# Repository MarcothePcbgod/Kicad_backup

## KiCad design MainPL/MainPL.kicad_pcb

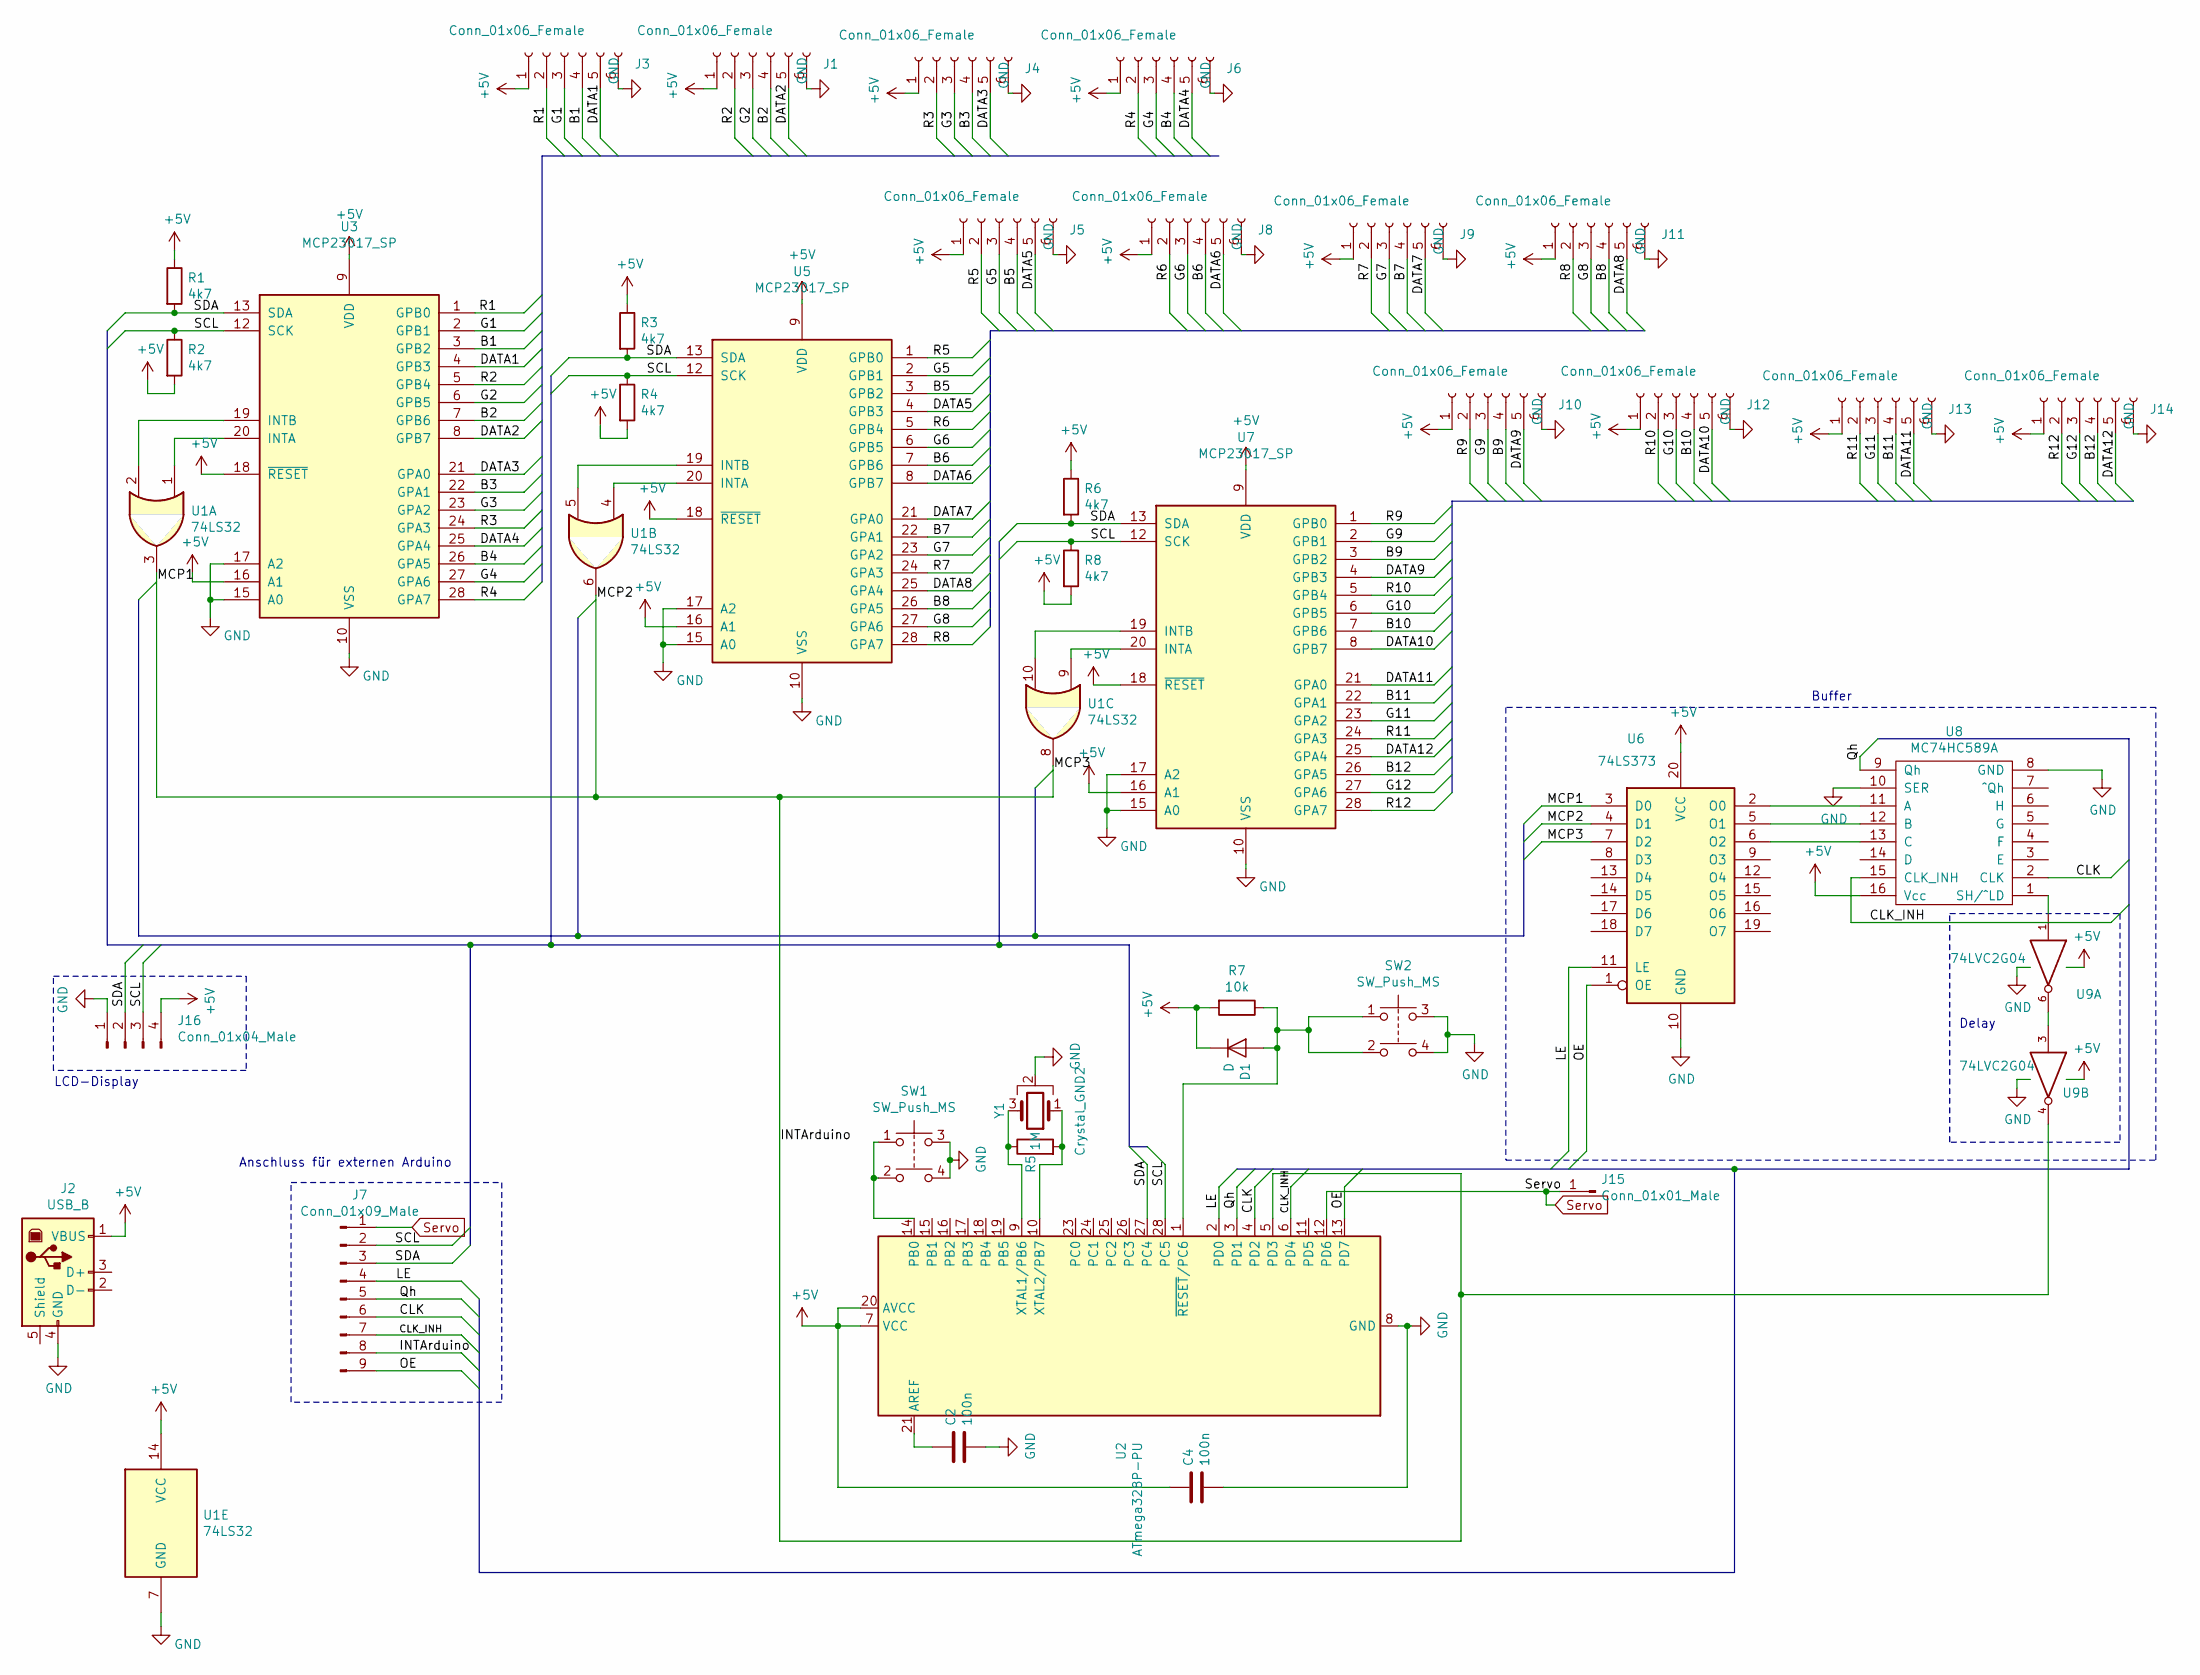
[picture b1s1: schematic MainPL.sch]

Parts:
C2, C4: 100n; C_0805_2012Metric_Pad1.15x1.40mm_HandSolder
D1: D; D_5W_P10.16mm_Horizontal
J1, J3, J4, J5, J6, J8, J9, J10, J11, J12, J13, J14: Conn_01x06_Female; PinHeader_1x06_P2.54mm_Vertical
J2: USB_B; USB_B_OST_USB-B1HSxx_Horizontal
J7: Conn_01x09_Male; PinHeader_1x09_P2.54mm_Vertical
J15: Conn_01x01_Male; PinHeader_1x01_P2.54mm_Vertical
J16: Conn_01x04_Male; PinHeader_1x04_P2.54mm_Horizontal
R1, R2, R3, R4, R6, R8: 4k7; R_1206_3216Metric_Pad1.42x1.75mm_HandSolder
R5: 1M; R_0805_2012Metric_Pad1.15x1.40mm_HandSolder
R7: 10k; R_0805_2012Metric_Pad1.15x1.40mm_HandSolder
SW1, SW2: SW_Push_MS; SW_TH_Tactile_Omron_B3F-10xx
U1: 74LS32; DIP-14_W7.62mm_Socket_LongPads
U2: ATmega328P-PU; DIP-28_W7.62mm_Socket_LongPads
U3, U5, U7: MCP23017_SP; DIP-28_W7.62mm_Socket_LongPads
U6: 74LS373; DIP-20_W7.62mm_Socket_LongPads
U8: MC74HC589A; DIP-16_W7.62mm_Socket_LongPads
U9: 74LVC2G04; DIP-6_W7.62mm_Socket_LongPads
Y1: Crystal_GND2; Crystal_HC49-U-3Pin_Vertical

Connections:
+5V: C4.1, D1.1 (K), J1.1, J2.1 (VBUS), J3.1, J4.1, J5.1, J6.1, J8.1, J9.1, J10.1, J11.1, J12.1, J13.1, J14.1, J16.4, R1.1, R2.2, R3.1, R4.2, R6.1, R7.2, R8.2, U1.14 (VCC), U2.7 (VCC), U2.20 (AVCC), U3.9 (VDD), U3.16 (A1), U3.18 (~RESET~), U5.9 (VDD), U5.16 (A1), U5.18 (~RESET~), U6.20 (VCC), U7.9 (VDD), U7.16 (A1), U7.18 (~RESET~), U8.16 (Vcc), U9.5 (VCC)
/B1: J3.4, U3.3 (GPB2)
/B2: J1.4, U3.7 (GPB6)
/B3: J4.4, U3.22 (GPA1)
/B4: J6.4, U3.26 (GPA5)
/B5: J5.4, U5.3 (GPB2)
/B6: J8.4, U5.7 (GPB6)
/B7: J9.4, U5.22 (GPA1)
/B8: J11.4, U5.26 (GPA5)
/B9: J10.4, U7.3 (GPB2)
/B10: J12.4, U7.7 (GPB6)
/B11: J13.4, U7.22 (GPA1)
/B12: J14.4, U7.26 (GPA5)
/CLK: J7.6, U2.4 (PD2), U8.2 (CLK)
/CLK_INH: J7.7, U2.6 (PD4), U8.15 (CLK_INH)
/DATA1: J3.5, U3.4 (GPB3)
/DATA2: J1.5, U3.8 (GPB7)
/DATA3: J4.5, U3.21 (GPA0)
/DATA4: J6.5, U3.25 (GPA4)
/DATA5: J5.5, U5.4 (GPB3)
/DATA6: J8.5, U5.8 (GPB7)
/DATA7: J9.5, U5.21 (GPA0)
/DATA8: J11.5, U5.25 (GPA4)
/DATA9: J10.5, U7.4 (GPB3)
/DATA10: J12.5, U7.8 (GPB7)
/DATA11: J13.5, U7.21 (GPA0)
/DATA12: J14.5, U7.25 (GPA4)
/G1: J3.3, U3.2 (GPB1)
/G2: J1.3, U3.6 (GPB5)
/G3: J4.3, U3.23 (GPA2)
/G4: J6.3, U3.27 (GPA6)
/G5: J5.3, U5.2 (GPB1)
/G6: J8.3, U5.6 (GPB5)
/G7: J9.3, U5.23 (GPA2)
/G8: J11.3, U5.27 (GPA6)
/G9: J10.3, U7.2 (GPB1)
/G10: J12.3, U7.6 (GPB5)
/G11: J13.3, U7.23 (GPA2)
/G12: J14.3, U7.27 (GPA6)
/INTArduino: J7.8, U1.3, U1.6, U1.8, U2.5 (PD3), U6.3 (D0), U6.4 (D1), U6.7 (D2), U9.4
/LE: J7.4, U2.2 (PD0), U6.11 (LE)
/OE: J7.9, U2.13 (PD7), U6.1 (OE)
/Qh: J7.5, U2.3 (PD1), U8.9 (Qh)
/R1: J3.2, U3.1 (GPB0)
/R2: J1.2, U3.5 (GPB4)
/R3: J4.2, U3.24 (GPA3)
/R4: J6.2, U3.28 (GPA7)
/R5: J5.2, U5.1 (GPB0)
/R6: J8.2, U5.5 (GPB4)
/R7: J9.2, U5.24 (GPA3)
/R8: J11.2, U5.28 (GPA7)
/R9: J10.2, U7.1 (GPB0)
/R10: J12.2, U7.5 (GPB4)
/R11: J13.2, U7.24 (GPA3)
/R12: J14.2, U7.28 (GPA7)
/SCL: J7.2, J16.3, R2.1, R4.1, R8.1, U2.28 (PC5), U3.12 (SCK), U5.12 (SCK), U7.12 (SCK)
/SDA: J7.3, J16.2, R1.2, R3.2, R6.2, U2.27 (PC4), U3.13 (SDA), U5.13 (SDA), U7.13 (SDA)
GND: C2.2, C4.2, J1.6, J2.4 (GND), J3.6, J4.6, J5.6, J6.6, J8.6, J9.6, J10.6, J11.6, J12.6, J13.6, J14.6, J16.1, SW1.3, SW1.4, SW2.3, SW2.4, U1.7 (GND), U2.8 (GND), U2.22 (GND), U3.10 (VSS), U3.15 (A0), U3.17 (A2), U5.10 (VSS), U5.15 (A0), U5.17 (A2), U6.10 (GND), U7.10 (VSS), U7.15 (A0), U7.17 (A2), U8.8 (GND), U8.10 (SER), U9.2 (GND), Y1.2
unnamed: C2.1, U2.21 (AREF)
unnamed: D1.2 (A), R7.1, SW2.1, SW2.2, U2.1 (~RESET~/PC6)
unnamed: R5.1, U2.9 (XTAL1/PB6), Y1.3
unnamed: R5.2, U2.10 (XTAL2/PB7), Y1.1
unnamed: SW1.1, SW1.2, U2.14 (PB0)
unnamed: U1.1, U3.20 (INTA)
unnamed: U1.2, U3.19 (INTB)
unnamed: U1.4, U5.20 (INTA)
unnamed: U1.5, U5.19 (INTB)
unnamed: U1.9, U7.20 (INTA)
unnamed: U1.10, U7.19 (INTB)
unnamed: U6.2 (O0), U8.11 (A)
unnamed: U6.5 (O1), U8.12 (B)
unnamed: U6.6 (O2), U8.13 (C)
unnamed: U8.1 (SH/^LD), U9.1
unnamed: U9.3, U9.6
Servo: J7.1, J15.1, U2.12 (PD6)

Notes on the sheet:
Anschluss für externen Arduino
Delay
Buffer
LCD-Display

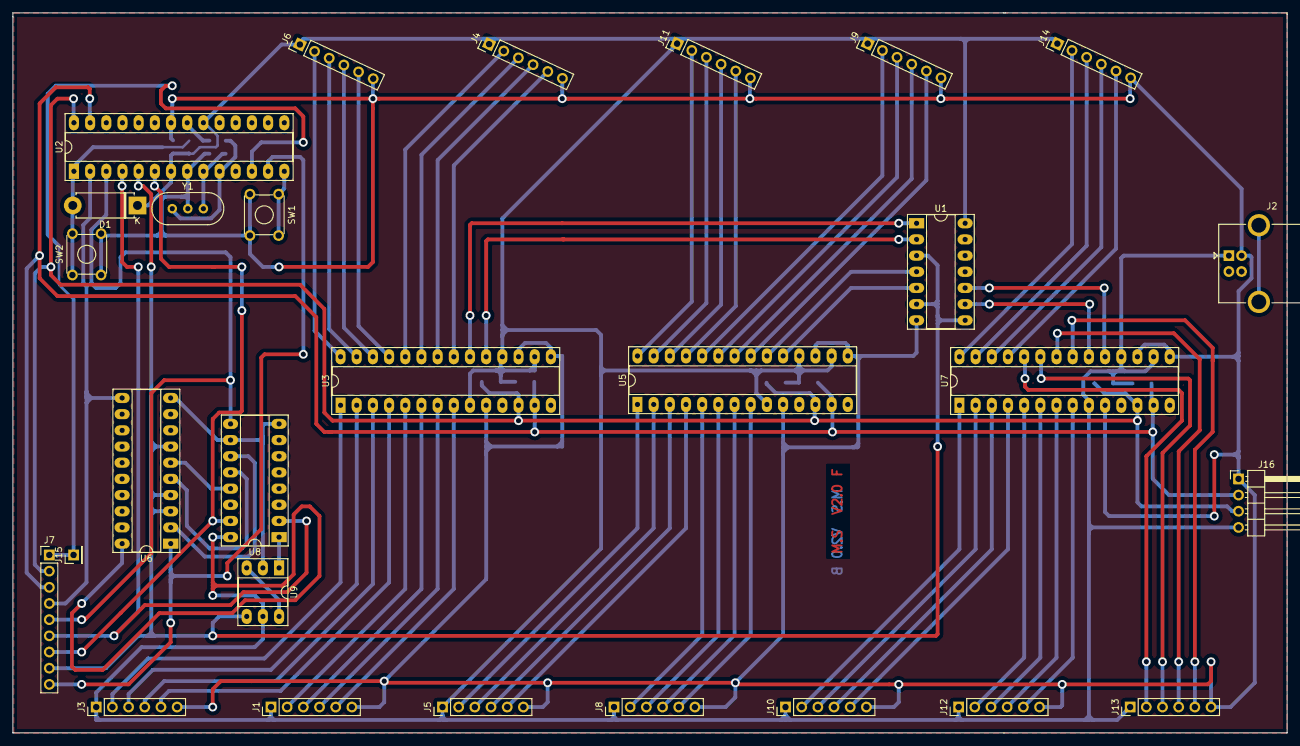
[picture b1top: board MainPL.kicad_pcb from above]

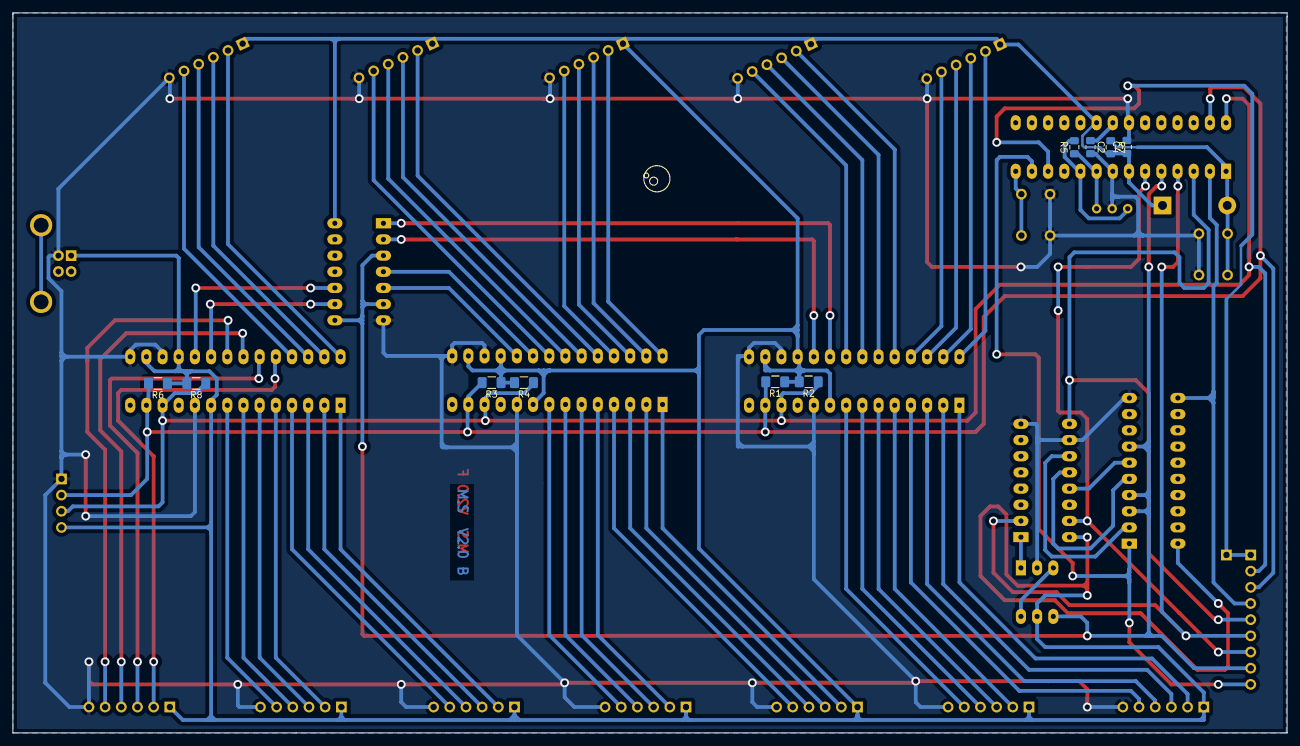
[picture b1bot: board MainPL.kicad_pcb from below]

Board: 2 copper layers, 200.0 x 113.0 mm, 38 parts (10 on the bottom side), 75 nets.

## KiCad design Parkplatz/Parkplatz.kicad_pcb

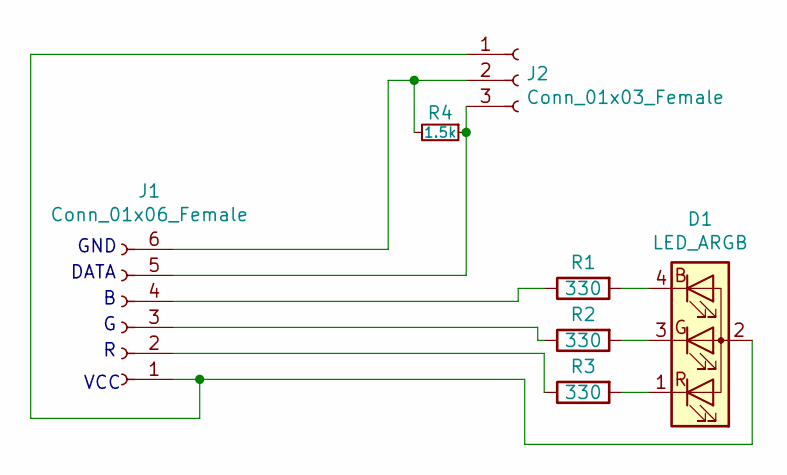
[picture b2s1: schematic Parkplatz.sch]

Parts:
D1: LED_ARGB; LED_D5.0mm-4_RGB
J1: Conn_01x06_Female; PinHeader_1x06_P2.54mm_Vertical
J2: Conn_01x03_Female; PinSocket_1x03_P2.54mm_Vertical
R1, R2, R3: 330; R_1206_3216Metric_Pad1.42x1.75mm_HandSolder
R4: 1.5k; R_1206_3216Metric_Pad1.42x1.75mm_HandSolder

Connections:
unnamed: D1.1 (RK), R3.2
unnamed: D1.2 (A), J1.1, J2.1
unnamed: D1.3 (GK), R2.2
unnamed: D1.4 (BK), R1.2
unnamed: J1.2, R3.1
unnamed: J1.3, R2.1
unnamed: J1.4, R1.1
unnamed: J1.5, J2.3, R4.1
unnamed: J1.6, J2.2, R4.2

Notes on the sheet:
GND
VCC
DATA

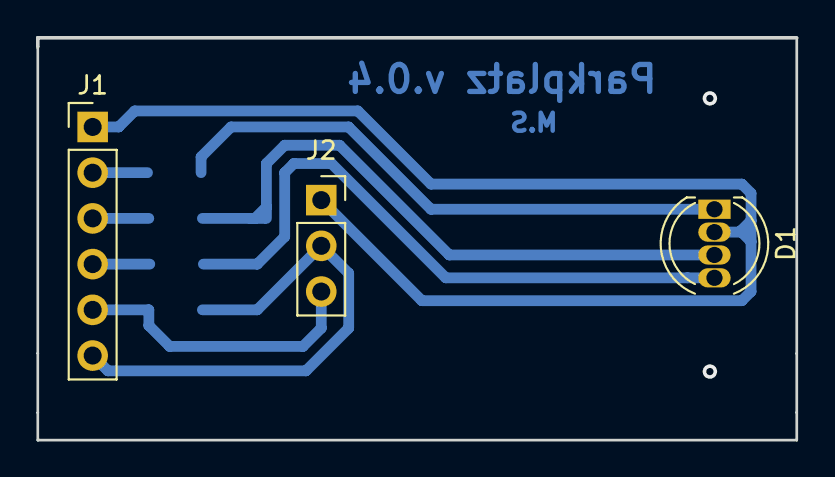
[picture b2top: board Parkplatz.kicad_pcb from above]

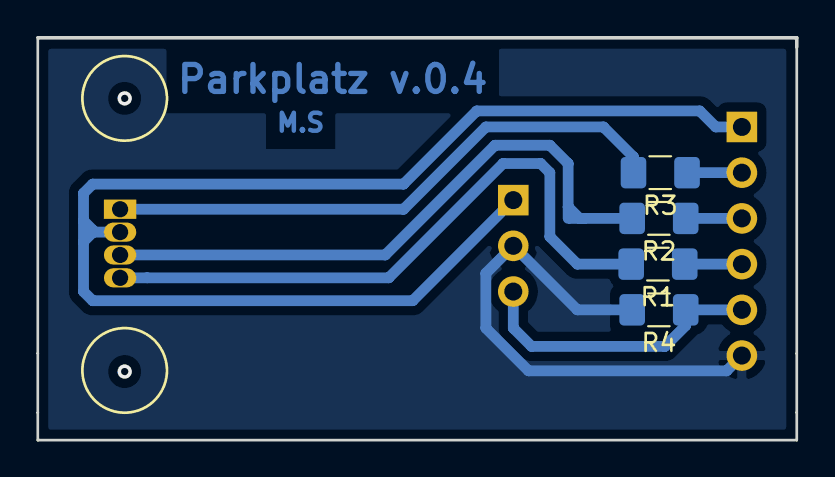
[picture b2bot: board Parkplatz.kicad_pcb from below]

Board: 2 copper layers, 42.2 x 22.3 mm, 7 parts (4 on the bottom side), 9 nets.

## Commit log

2019-12-18 Add files via upload
    Schaltplan fertig
2019-12-19 Add files via upload
    Bemaßung bei Pcb fertig und Pcb begonnen
2019-12-19 Parkplatzmodul
2019-12-24 Modul überarbeitet
2019-12-24 Pcb weiter
2019-12-24 SCL und SCK und Arduino fehlt
2019-12-24 Arduino fehlt noch
2019-12-25 Screen des Main Schematics hinzugefügt - Code
2020-01-07 Verbesserung fehlt
2020-01-07 Verbesserung machen
2020-01-10 File gefixed
2020-01-12 Änderung der Ints und leichte Verbesserung
2020-01-13 MainPL fertig
2020-01-21 Add files via upload
    V.2 von Parkplatz mit neuen Maßen
2020-01-21 Neues Pcb fertig
2020-01-27 Beschriftung eingefügt
